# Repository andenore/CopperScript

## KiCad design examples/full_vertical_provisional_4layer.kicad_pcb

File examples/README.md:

# CopperScript examples

Each standalone example owns a directory so its source, local assets and
generated reference inputs stay together. The reusable component
packages under `packages/` are separate from these board and language examples.

| Example | Entry point |
| --- | --- |
| Antenna synthesis probe (first-order monopole template) | `antenna_synthesis/board.copper` |
| Coupling probe (antenna to a routed clock, `copper coupling`) | `coupling/board.copper` |
| Copper hard-macro definition | `macro_definition/board.copper` |
| Device model showcase | `device_model_showcase/board.copper` |
| Full vertical integration board | `full_vertical/board.copper` |
| FX10-like USB bridge, 121-ball 0.8 mm BGA (routing benchmark) | `fx10_bridge/board.copper` |
| Hierarchical board | `hierarchical_board/board.copper` |
| Invalid diagnostics fixture | `invalid_board/board.copper` |
| Mechanical anchors | `mechanical_anchors/board.copper` |
| Mechanical curves | `mechanical_curves/board.copper` |
| Mechanical editor demo | `mechanical_editor_demo/board.copper` |
| Mechanical outline | `mechanical_outline/board.copper` |
| Mechanical reference assets | `mechanical_reference/board.copper` |
| nRF52832 coin-cell board | `nrf52_coin_cell/board.copper` |
| nRF antenna hard-macro probe | `nrf_antenna_macro/board.copper` |
| TPS62130A regulator hard-macro probe | `tps62130a_macro/board.copper` |
| Resolved local footprint | `resolved_footprint_board/board.copper` |
| Valid compiler fixture | `valid_board/board.copper` |
| Analog front end (simulation removed) | [Source and recorded evidence](simulation/analog_frontend/README.md) |
| Soil impedance analyzer: battery board with the analog front end as a module, benches for the module | [Specification](simulation/impedance_analyzer/SPEC.md), [board, benches and results](simulation/impedance_analyzer/README.md) |
| Low-noise preamp: noise, Monte Carlo gain and worst-case offset benches | `simulation/preamp/board.copper` |
| Precision rectifier: a transient bench with a diode, op-amp clipping and slew, THD | `simulation/precision_rectifier/board.copper` |
| SPICE amplifier: an op-amp from a self-written SPICE model file (`sim spice`), op, AC, tran and noise benches | `simulation/spice_amplifier/board.copper` |
| Vendor models: TI's OPA810 PSpice model by URL and SHA-256 beside the built-in macro model (needs `copper models fetch`) | `simulation/vendor_models/board.copper` |

The CM4 carrier, managed-footprint, and simulation examples already use
multi-file directories and retain their existing folder names.

For a complete LED-ring board project, use
[CopperLedRing](https://github.com/andenore/CopperLedRing). It owns the current
board source, exact component selections, dependency pins and routing evidence.
Follow that project's build instructions and qualification status; its recorded
routing pass does not imply fabrication readiness.

Physical macro examples declare their bindings in `.copper` with ordinary asset
imports. Versions and hashes use the existing dependency workflow; the compiler
places and materializes those declarations without separately loading macro
scenes.

## Deprecated fixtures

`round_led_ring/board.copper` is deprecated in favor of CopperLedRing. It
remains for compiler regression tests and existing
commands, not as a second maintained LED-ring design or a routing benchmark.
See the [legacy fixture notes](../docs/round-led-ring.md).

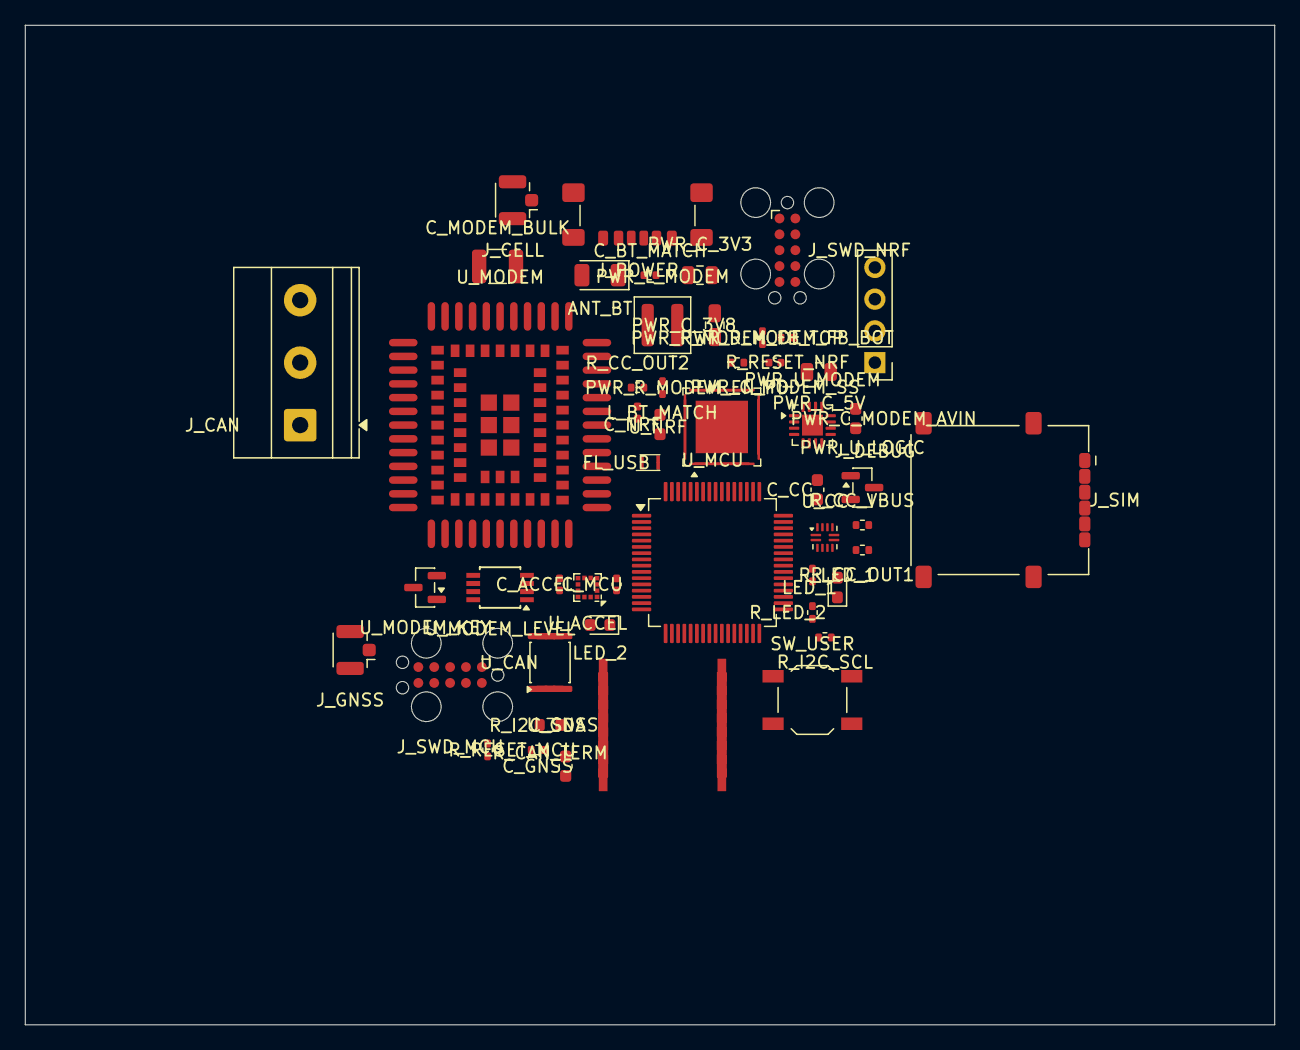
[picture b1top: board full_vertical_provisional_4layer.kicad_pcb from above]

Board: 4 copper layers, 100.0 x 80.0 mm, 51 parts (0 on the bottom side), 58 nets, no tracks yet.

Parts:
ANT_BT: RF_ANTENNA; Johanson_2450AT18x100
C_ACCEL: 1E+2 nF; C_0402_1005Metric
C_BT_MATCH: 0.8 pF; C_0402_1005Metric
C_CC: 1 uF; C_0603_1608Metric
C_GNSS: 1 uF; C_0603_1608Metric
C_MCU: 1E+2 nF; C_0402_1005Metric
C_MODEM_BULK: 1E+2 uF; C_1210_3225Metric
C_NRF: 4.7 uF; C_0603_1608Metric
FL_USB: COILCRAFT_0603USB_601MLC; L_CommonModeChoke_Coilcraft_0603USB
J_CAN: CAN_CONNECTOR; TerminalBlock_Phoenix_MKDS-1,5-3_1x03_P5.00mm_Horizontal
J_CELL: RF_CONNECTOR; U.FL_Hirose_U.FL-R-SMT-1_Vertical
J_DEBUG: DEBUG_UART_HEADER; PinHeader_1x04_P2.54mm_Vertical
J_GNSS: RF_CONNECTOR; U.FL_Hirose_U.FL-R-SMT-1_Vertical
J_POWER: GCT_USB4135_GF_A; USB_C_Receptacle_GCT_USB4135-GF-A_6P_TopMnt_Horizontal
J_SIM: SIM8060_6_0_14_00_A; nanoSIM_GCT_SIM8060-6-0-14-00
J_SWD_MCU: SWD_HEADER; Tag-Connect_TC2050-IDC-FP_2x05_P1.27mm_Vertical
J_SWD_NRF: SWD_HEADER; Tag-Connect_TC2050-IDC-FP_2x05_P1.27mm_Vertical
LED_1, LED_2: LED; LED_0603_1608Metric
L_BT_MATCH: 3.9 nH; L_0402_1005Metric
PWR_C_3V3, PWR_C_3V8: 22 uF; C_0805_2012Metric
PWR_C_5V: 1E+1 uF; C_0805_2012Metric
PWR_C_MODEM_AVIN: 1E+2 nF; C_0603_1608Metric
PWR_C_MODEM_SS: 3.3 nF; C_0402_1005Metric
PWR_L_MODEM: XAL4020_222MEC; L_Coilcraft_XAL4020-XXX
PWR_R_MODEM_EN_PD: 1E+2 kohm; R_0402_1005Metric
PWR_R_MODEM_FB_BOT: 2E+2 kohm; R_0402_1005Metric
PWR_R_MODEM_FB_TOP: 7.5E+2 kohm; R_0402_1005Metric
PWR_U_LOGIC: REGULATOR_3V3; SOT-23
PWR_U_MODEM: TPS62130ARGTR; VQFN-16-1EP_3x3mm_P0.5mm_EP1.68x1.68mm
R_CAN_TERM: 1.2E+2 ohm; R_0603_1608Metric
R_CC_OUT1, R_CC_OUT2: 1E+1 kohm; R_0402_1005Metric
R_CC_VBUS: 9E+2 kohm; R_0402_1005Metric
R_I2C_SCL, R_I2C_SDA: 4.7 kohm; R_0402_1005Metric
R_LED_1, R_LED_2: 1 kohm; R_0402_1005Metric
R_RESET_MCU: 1E+1 kohm; R_0402_1005Metric
R_RESET_NRF: 1E+1 kohm; R_0402_1005Metric
SW_USER: BUTTON; SW_SPST_TL3342
U_ACCEL: LIS2DW12; LGA-12_2x2mm_P0.5mm
U_CAN: TCAN334G; VSSOP-8_3x3mm_P0.65mm
U_CC: TUSB320LAI; Texas_X2QFN-12_1.6x1.6mm_P0.4mm
U_GNSS: MAX_M10S_00B; u-blox_MAX-M10S
U_MCU: STM32G0C1RET6; LQFP-64_10x10mm_P0.5mm
U_MODEM: EG800G_EU; Quectel_EG800G
U_MODEM_KEY: OPEN_DRAIN_DRIVER; SOT-23
U_MODEM_LEVEL: DUAL_UART_LEVEL_SHIFTER; TSSOP-8_3x3mm_P0.65mm
U_NRF: NRF52832_QFAA; QFN-48-1EP_6x6mm_P0.4mm_EP4.2x4.2mm

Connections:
ACCEL_INT: U_ACCEL.12, U_MCU.15
CAN_H: J_CAN.1, R_CAN_TERM.1, U_CAN.7
CAN_L: J_CAN.2, R_CAN_TERM.2, U_CAN.6
CAN_RX: U_CAN.4, U_MCU.25
CAN_TX: U_CAN.1, U_MCU.26
CELL_RF: J_CELL.1, U_MODEM.35
DEBUG_RX: J_DEBUG.3, U_MCU.22
DEBUG_TX: J_DEBUG.2, U_MCU.21
GND: ANT_BT.2, C_ACCEL.2, C_BT_MATCH.2, C_CC.2, C_GNSS.2, C_MCU.2, C_MODEM_BULK.2, C_NRF.2, J_CAN.3, J_CELL.2, J_DEBUG.4, J_GNSS.2, J_POWER.A12, J_POWER.B12, J_POWER.SH, J_SIM.5, J_SIM.SH, J_SWD_MCU.3, J_SWD_MCU.5, J_SWD_NRF.3, J_SWD_NRF.5, LED_1.2, LED_2.2, PWR_C_3V3.2, PWR_C_3V8.2, PWR_C_5V.2, PWR_C_MODEM_AVIN.2, PWR_C_MODEM_SS.2, PWR_R_MODEM_EN_PD.2, PWR_R_MODEM_FB_BOT.2, PWR_U_LOGIC.2, PWR_U_MODEM.6, PWR_U_MODEM.7, PWR_U_MODEM.8, PWR_U_MODEM.15, PWR_U_MODEM.16, PWR_U_MODEM.17, SW_USER.2, U_ACCEL.3, U_ACCEL.6, U_ACCEL.7, U_ACCEL.8, U_CAN.2, U_CAN.5, U_CAN.8, U_CC.3, U_CC.10, U_CC.11, U_GNSS.1, U_GNSS.10, U_GNSS.12, U_MCU.9, U_MODEM.1, U_MODEM.10, U_MODEM.27, U_MODEM.34, U_MODEM.36, U_MODEM.37, U_MODEM.40, U_MODEM.41, U_MODEM.45, U_MODEM.46, U_MODEM.47, U_MODEM.48, U_MODEM.70, U_MODEM.71, U_MODEM.72, U_MODEM.73, U_MODEM.88, U_MODEM.89, U_MODEM.90, U_MODEM.91, U_MODEM.92, U_MODEM.93, U_MODEM.94, U_MODEM.95, U_MODEM_KEY.2, U_MODEM_LEVEL.4, U_NRF.31, U_NRF.45, U_NRF.49
GNSS_RF: J_GNSS.1, U_GNSS.11
GNSS_RX: U_GNSS.3, U_MCU.19
GNSS_TIMEPULSE: U_GNSS.4, U_MCU.16
GNSS_TX: U_GNSS.2, U_MCU.20
I2C_SCL: R_I2C_SCL.2, U_ACCEL.1, U_MCU.24
I2C_SDA: R_I2C_SDA.2, U_ACCEL.4, U_MCU.23
MCU_MODEM_RX: U_MCU.61, U_MODEM_LEVEL.3
MCU_MODEM_TX: U_MCU.60, U_MODEM_LEVEL.2
MCU_NRF_RX: U_MCU.63, U_NRF.8
MCU_NRF_TX: U_MCU.62, U_NRF.10
MCU_RESET: J_SWD_MCU.10, R_RESET_MCU.2, U_MCU.12
MCU_SWDCLK: J_SWD_MCU.4, U_MCU.46
MCU_SWDIO: J_SWD_MCU.2, U_MCU.45
MODEM_EN: PWR_R_MODEM_EN_PD.1, PWR_U_MODEM.13, U_MCU.64
MODEM_PWRKEY: U_MODEM.7, U_MODEM_KEY.3
MODEM_PWRKEY_CTL: U_MCU.13, U_MODEM_KEY.1
MODEM_STATUS: U_MCU.14, U_MODEM.25
MODEM_UART_RX: U_MODEM.17, U_MODEM_LEVEL.5
MODEM_UART_TX: U_MODEM.18, U_MODEM_LEVEL.6
NRF_RESET: J_SWD_NRF.10, R_RESET_NRF.2, U_NRF.24
NRF_RF_ANT: ANT_BT.1, C_BT_MATCH.1, L_BT_MATCH.2
NRF_RF_RAW: L_BT_MATCH.1, U_NRF.30
NRF_SWDCLK: J_SWD_NRF.4, U_NRF.25
NRF_SWDIO: J_SWD_NRF.2, U_NRF.26
PWR/MODEM_FB: PWR_R_MODEM_FB_BOT.1, PWR_R_MODEM_FB_TOP.2, PWR_U_MODEM.5
PWR/MODEM_SS: PWR_C_MODEM_SS.1, PWR_U_MODEM.9
PWR/MODEM_SW: PWR_L_MODEM.1, PWR_U_MODEM.1, PWR_U_MODEM.2, PWR_U_MODEM.3
SIM_CLK: J_SIM.3, U_MODEM.13
SIM_IO: J_SIM.7, U_MODEM.11
SIM_RST: J_SIM.2, U_MODEM.12
SIM_VCC: J_SIM.1, U_MODEM.14
USB_C_CC1: J_POWER.A5, U_CC.1
USB_C_CC2: J_POWER.B5, U_CC.2
USB_C_CURRENT_1: R_CC_OUT1.2, U_CC.7, U_MCU.48
USB_C_CURRENT_2: R_CC_OUT2.2, U_CC.8, U_MCU.49
USB_C_VBUS_DET: R_CC_VBUS.2, U_CC.4
USB_DM_MCU: FL_USB.2, U_MCU.43
USB_DM_MODEM: FL_USB.3, U_MODEM.60
USB_DP_MCU: FL_USB.1, U_MCU.44
USB_DP_MODEM: FL_USB.4, U_MODEM.59
USER_BUTTON: SW_USER.1, U_MCU.3
USER_LED_1: R_LED_1.1, U_MCU.38
USER_LED_1_A: LED_1.1, R_LED_1.2
USER_LED_2: R_LED_2.1, U_MCU.39
USER_LED_2_A: LED_2.1, R_LED_2.2
V1V8_MODEM: U_MODEM.24, U_MODEM_LEVEL.8
V3V3: C_ACCEL.1, C_CC.1, C_GNSS.1, C_MCU.1, C_NRF.1, J_DEBUG.1, J_SWD_MCU.1, J_SWD_NRF.1, PWR_C_3V3.1, PWR_U_LOGIC.3, R_CC_OUT1.1, R_CC_OUT2.1, R_I2C_SCL.1, R_I2C_SDA.1, R_RESET_MCU.1, R_RESET_NRF.1, U_ACCEL.2, U_ACCEL.9, U_ACCEL.10, U_CAN.3, U_CC.12, U_GNSS.6, U_GNSS.7, U_GNSS.8, U_MCU.6, U_MCU.7, U_MCU.8, U_MODEM_LEVEL.1, U_MODEM_LEVEL.7, U_NRF.13, U_NRF.36, U_NRF.48
V3V8: C_MODEM_BULK.1, PWR_C_3V8.1, PWR_L_MODEM.2, PWR_R_MODEM_FB_TOP.1, PWR_U_MODEM.14, U_MODEM.42, U_MODEM.43
V5: J_POWER.A9, J_POWER.B9, PWR_C_5V.1, PWR_C_MODEM_AVIN.1, PWR_U_LOGIC.1, PWR_U_MODEM.10, PWR_U_MODEM.11, PWR_U_MODEM.12, R_CC_VBUS.1, U_MODEM.61

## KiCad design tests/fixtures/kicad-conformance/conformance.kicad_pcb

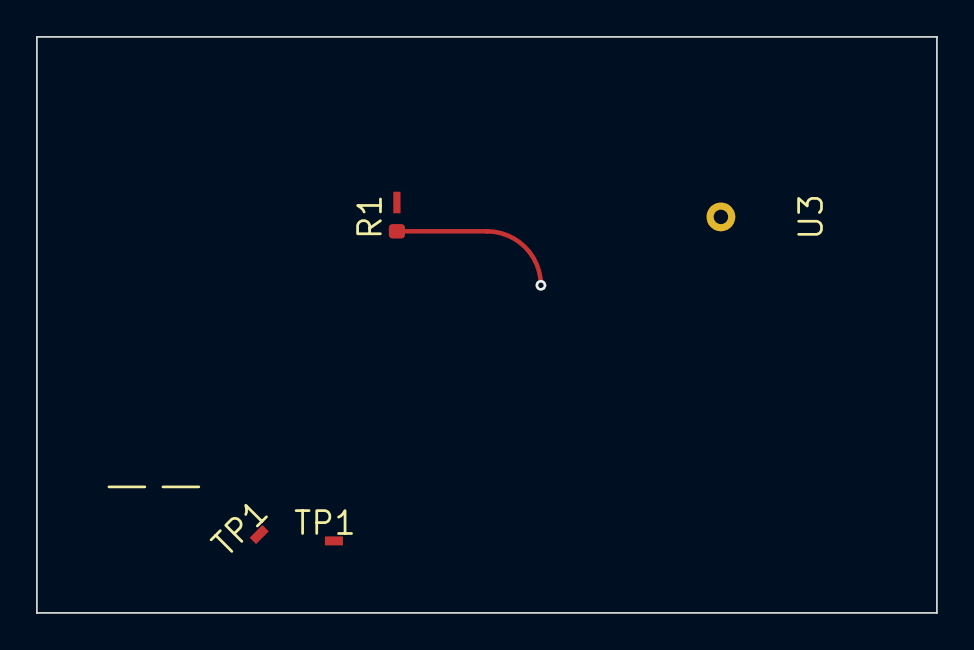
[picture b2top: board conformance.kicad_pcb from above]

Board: 2 copper layers, 50.0 x 32.0 mm, 5 parts (1 on the bottom side), 2 nets.

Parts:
R1: 10k; R_0603
TP1, TP1#2: TestPoint
U2: SOT23_Back
U3: Module_Keepout

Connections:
GND: R1.1, U2.3, U3.1
SIG: R1.2, TP1.1, TP1#2.1, U2.1

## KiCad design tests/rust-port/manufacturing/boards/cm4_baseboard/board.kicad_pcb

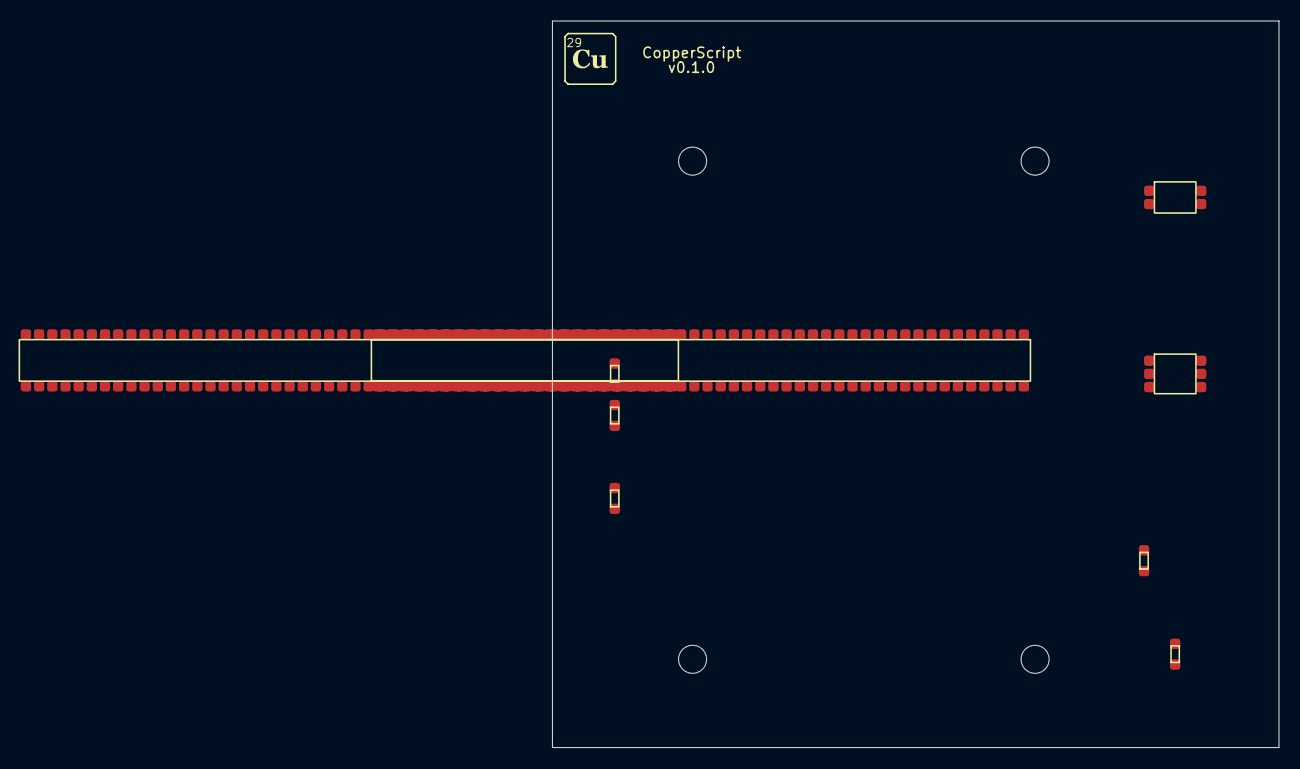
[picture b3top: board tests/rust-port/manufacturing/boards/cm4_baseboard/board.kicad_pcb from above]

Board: 4 copper layers, 70.0 x 70.0 mm, 13 parts (0 on the bottom side), 12 nets, no tracks yet.

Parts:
CS_MH_4e76aa086c1c0c76, CS_MH_46dff4b017b65127, CS_MH_57f5d33d8441581a: mechanical_hole_2700000__704487c97c5e890e1efa
CS_MH_a25b90a7272961f0: mechanical_hole_2700000__704487c97c5e890e1efa
C_VREF: 100 nF; Capacitor_SMD_C_0402_1005Metric_3bdc543a41__36df095855c7baa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
D1: KENTO_KT0603R; KENTO_KENTO_KT0603R_c41109b3dd__5e56d2dd6d7a4f36240d
J_CM4_GPIO, J_CM4_HS: DF40C-100DS-0.4V(51); github_com_andenore_CopperLib_packages_profiles_raspberry_p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
J_ENABLE: GLOBAL_EN / GND: short to power off; Connector_PinHeader_2_54mm_PinHeader_1x02_P2_54mm_Vertical_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
J_GPIO: 3V3 / GPIO2 / GPIO3 / GPIO17 / GPIO27 / GND; Connector_PinHeader_2_54mm_PinHeader_1x06_P2_54mm_Vertical_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
J_POWER: 5V IN / GND; Connector_PinHeader_2_54mm_PinHeader_1x02_P2_54mm_Vertical_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
J_UART: 3V3 sense / TX / RX / GND; Connector_PinHeader_2_54mm_PinHeader_1x04_P2_54mm_Vertical_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
R_LED: 10 kohm; Resistor_SMD_R_0603_1608Metric_4cb9c1d429__23516488a272ae66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

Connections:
ACT_LED_A: D1.1, R_LED.2
ACT_LED_K: D1.2, J_CM4_GPIO.21
CM4_RX: J_CM4_GPIO.51, J_UART.3
CM4_TX: J_CM4_GPIO.55, J_UART.2
GLOBAL_EN: J_CM4_GPIO.99, J_ENABLE.1
GND: C_VREF.2, J_CM4_GPIO.1, J_CM4_GPIO.2, J_CM4_GPIO.7, J_CM4_GPIO.8, J_CM4_GPIO.13, J_CM4_GPIO.14, J_CM4_GPIO.22, J_CM4_GPIO.23, J_CM4_GPIO.32, J_CM4_GPIO.33, J_CM4_GPIO.42, J_CM4_GPIO.43, J_CM4_GPIO.52, J_CM4_GPIO.53, J_CM4_GPIO.59, J_CM4_GPIO.60, J_CM4_GPIO.65, J_CM4_GPIO.66, J_CM4_GPIO.71, J_CM4_GPIO.74, J_CM4_GPIO.98, J_CM4_HS.7, J_CM4_HS.8, J_CM4_HS.13, J_CM4_HS.14, J_CM4_HS.19, J_CM4_HS.20, J_CM4_HS.25, J_CM4_HS.26, J_CM4_HS.31, J_CM4_HS.32, J_CM4_HS.37, J_CM4_HS.38, J_CM4_HS.44, J_CM4_HS.50, J_CM4_HS.55, J_CM4_HS.56, J_CM4_HS.61, J_CM4_HS.62, J_CM4_HS.67, J_CM4_HS.68, J_CM4_HS.73, J_CM4_HS.74, J_CM4_HS.79, J_CM4_HS.80, J_CM4_HS.85, J_CM4_HS.86, J_CM4_HS.91, J_CM4_HS.92, J_CM4_HS.97, J_CM4_HS.98, J_ENABLE.2, J_GPIO.6, J_POWER.2, J_UART.4
GPIO2: J_CM4_GPIO.58, J_GPIO.2
GPIO3: J_CM4_GPIO.56, J_GPIO.3
GPIO17: J_CM4_GPIO.50, J_GPIO.4
GPIO27: J_CM4_GPIO.48, J_GPIO.5
V3V3: C_VREF.1, J_CM4_GPIO.78, J_CM4_GPIO.84, J_CM4_GPIO.86, J_GPIO.1, J_UART.1, R_LED.1
V5: J_CM4_GPIO.77, J_CM4_GPIO.79, J_CM4_GPIO.81, J_CM4_GPIO.83, J_CM4_GPIO.85, J_CM4_GPIO.87, J_POWER.1

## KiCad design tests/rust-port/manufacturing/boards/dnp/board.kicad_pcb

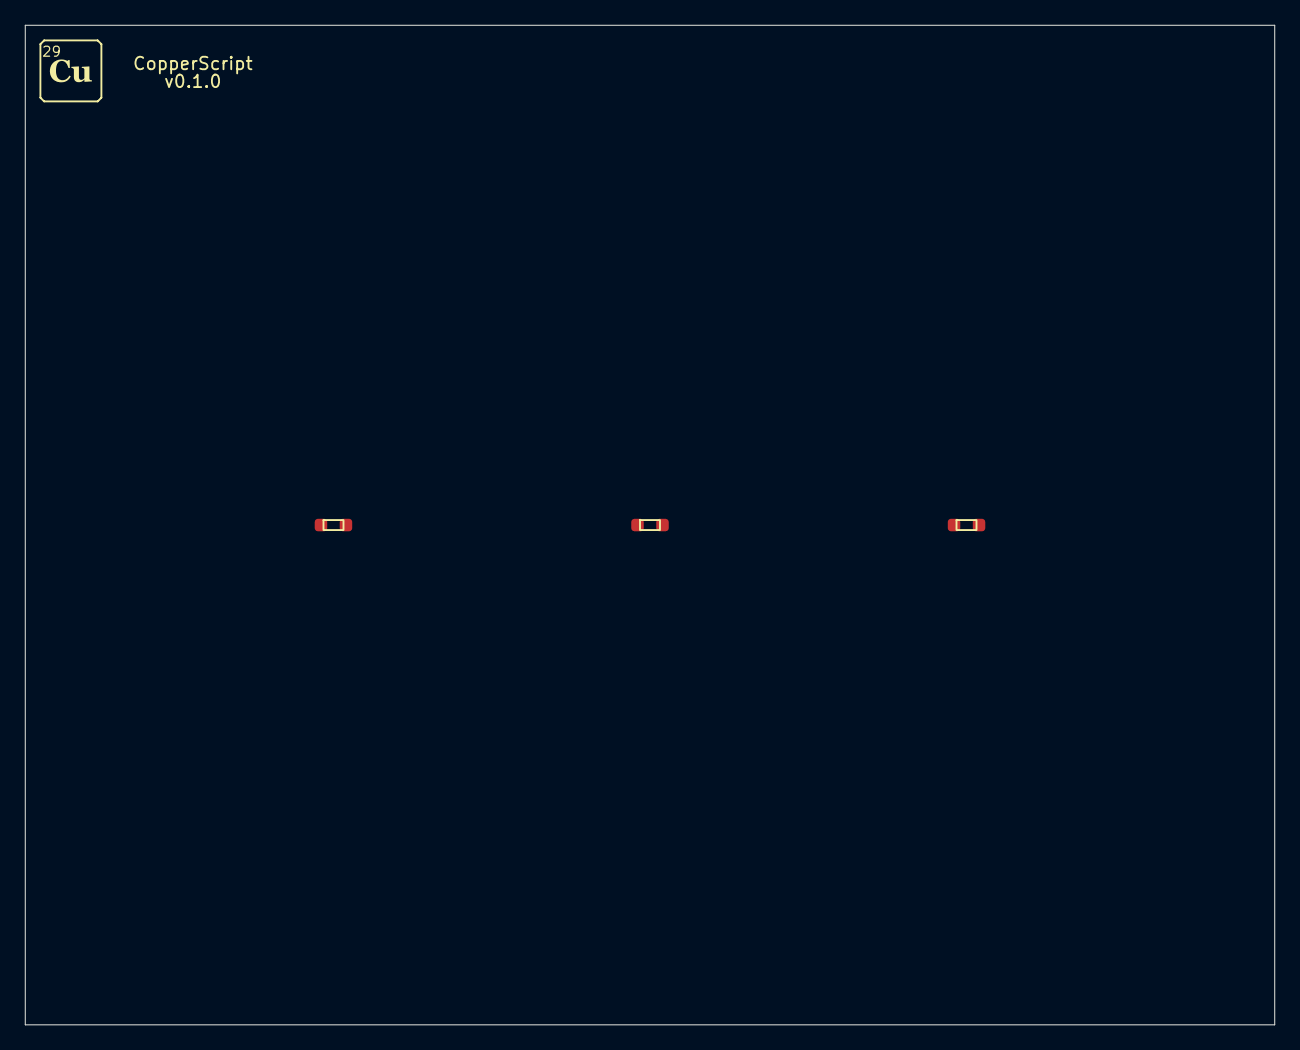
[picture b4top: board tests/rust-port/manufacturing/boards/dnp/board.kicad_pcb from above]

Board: 2 copper layers, 100.0 x 80.0 mm, 3 parts (0 on the bottom side), 2 nets, no tracks yet.

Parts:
C_DNP: DNP; Resistor_SMD_R_0402_1005Metric_fdb7f701ac__unassembled__f69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
R1, R2: Fitted; Resistor_SMD_R_0402_1005Metric_ea21fd0be2__078150e45b6b77ac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

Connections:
GND: C_DNP.2, R1.2, R2.2
SIGNAL: C_DNP.1, R1.1, R2.1

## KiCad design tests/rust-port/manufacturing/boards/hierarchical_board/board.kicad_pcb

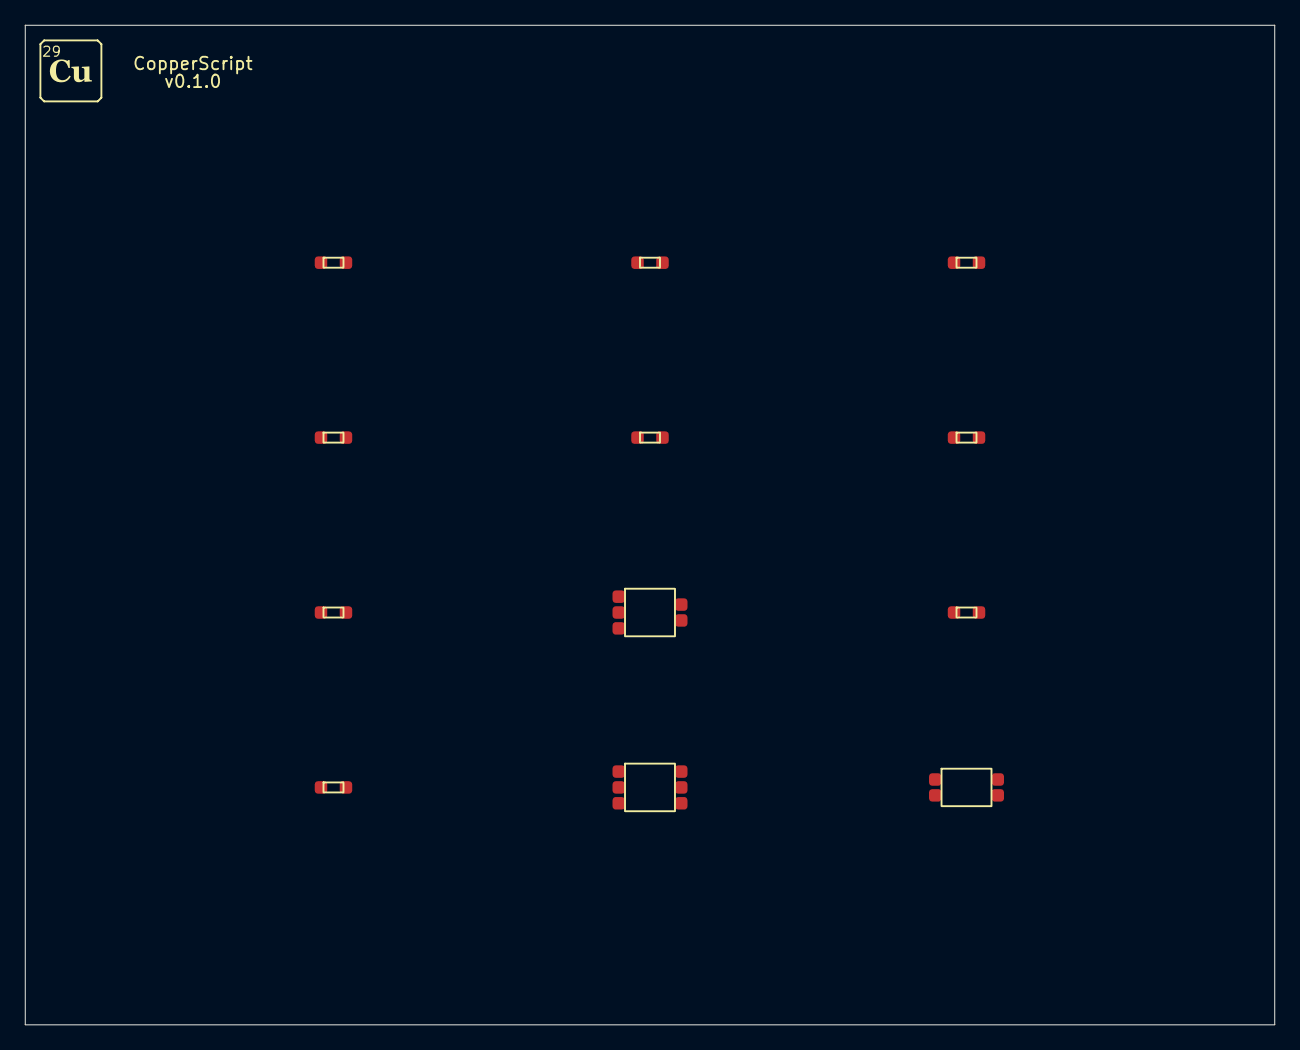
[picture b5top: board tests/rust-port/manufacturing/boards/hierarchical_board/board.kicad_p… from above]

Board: 2 copper layers, 100.0 x 80.0 mm, 12 parts (0 on the bottom side), 7 nets, no tracks yet.

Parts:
C1: 100 nF; 0402_9c2134b530__0fb0bb9a2e0077d858db
PWR_C_IN: 10 uF; 0603_81c387e6e1__c7736b0d8ecf520b0523
PWR_C_OUT: 22 uF; 0603_81c387e6e1__c7736b0d8ecf520b0523
PWR_D1: 40 V Schottky; SOD_123_efa837de2e__cfb0d4e968d0b264e214
PWR_L1: 10 uH; L_4x4mm_7af7df88b8__6a048950ee45cd71650c
PWR_R_BOTTOM: 31.6 kohm; 0402_b4527f9b21__9b192bf2ecd33fdeea18
PWR_R_TOP: 100 kohm; 0402_b4527f9b21__9b192bf2ecd33fdeea18
PWR_U1: 5 V to 3.3 V buck; SOT_23_5_1a109a2ec2__6e889cd8a0e923c7e456
R1, R2: 4.7 kohm; 0402_b4527f9b21__9b192bf2ecd33fdeea18
U1: STM32G0B1CBT6; LQFP_48_f42af30189__71b94d8e6008976dbf1f
U2: BME280; LGA_8_40352dfb0d__fcaac17623b50b27bffa

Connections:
GND: C1.2, PWR_C_IN.2, PWR_C_OUT.2, PWR_D1.1, PWR_R_BOTTOM.2, PWR_U1.2, U1.23, U2.2
I2C_SCL: R2.2, U1.45, U2.3
I2C_SDA: R1.2, U1.46, U2.4
PWR/FEEDBACK: PWR_R_BOTTOM.1, PWR_R_TOP.2, PWR_U1.4
PWR/SWITCH: PWR_D1.2, PWR_L1.1, PWR_U1.3
V3V3: C1.1, PWR_C_OUT.1, PWR_L1.2, PWR_R_TOP.1, R1.1, R2.1, U1.24, U2.1
VBUS: PWR_C_IN.1, PWR_U1.1, PWR_U1.5

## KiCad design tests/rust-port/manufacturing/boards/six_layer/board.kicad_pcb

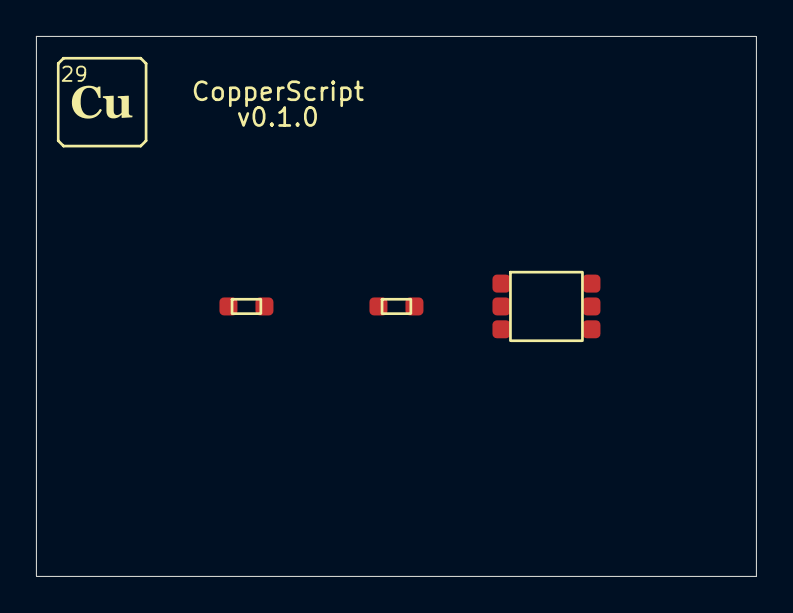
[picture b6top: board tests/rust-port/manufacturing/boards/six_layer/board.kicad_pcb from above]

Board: 6 copper layers, 40.0 x 30.0 mm, 3 parts (0 on the bottom side), 2 nets, no tracks yet.

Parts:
C1: 100 nF; 0402_9c2134b530__0fb0bb9a2e0077d858db
PS1: VOLTAGE_SOURCE; SOT_23_b818d02061__00451b3eeeeeadf5b295
U1: STM32_LIKE; LQFP_48_1857f4a7dd__18a179d3975fdd3a79ec

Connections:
GND: C1.2, PS1.2, U1.2
V3V3: C1.1, PS1.1, U1.1

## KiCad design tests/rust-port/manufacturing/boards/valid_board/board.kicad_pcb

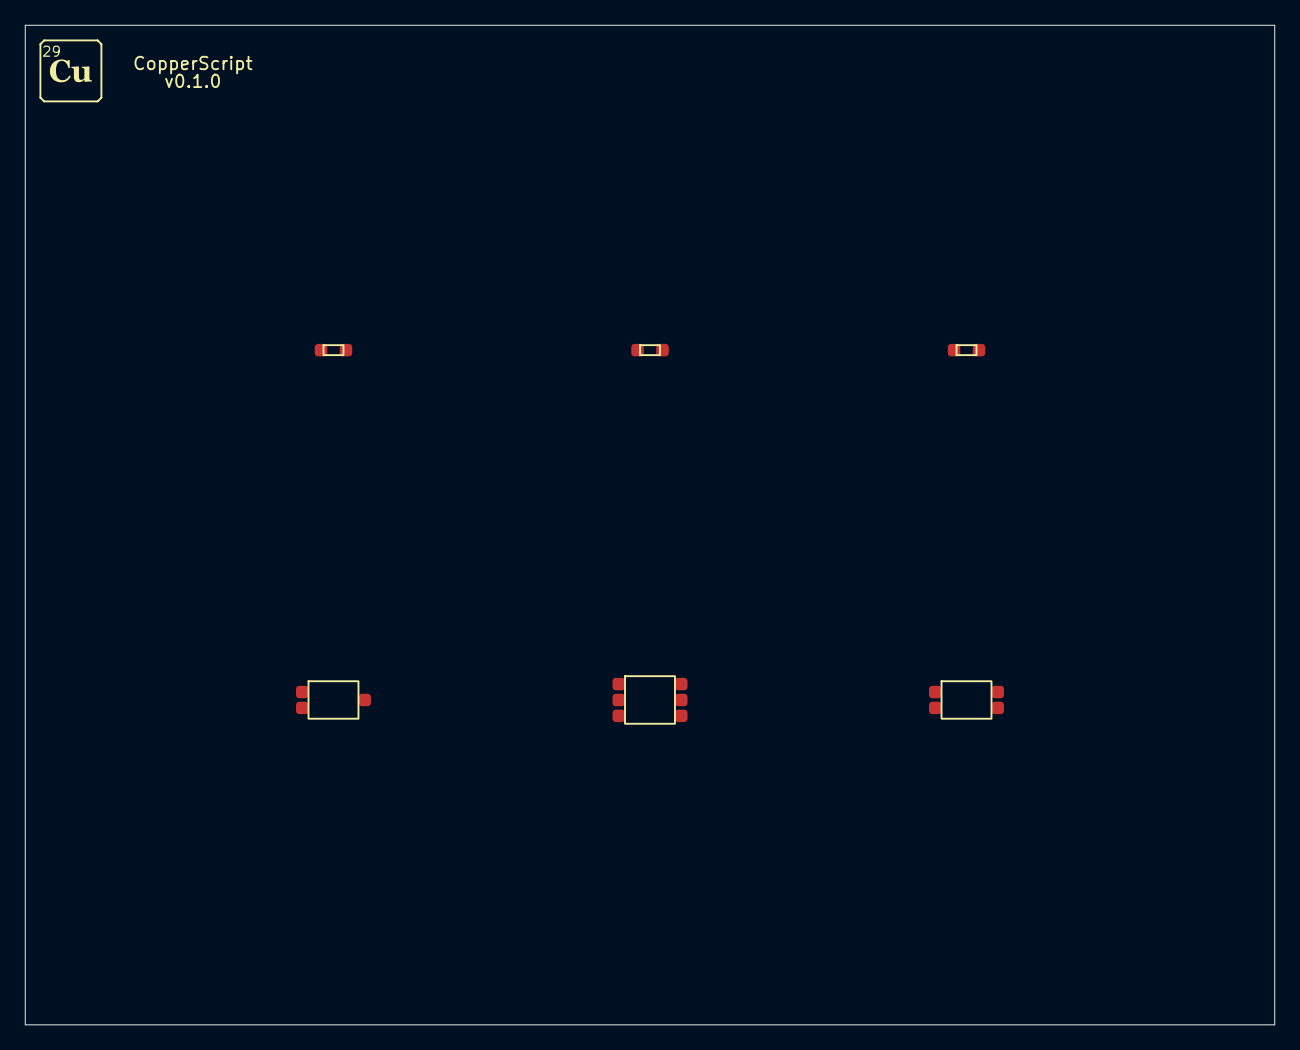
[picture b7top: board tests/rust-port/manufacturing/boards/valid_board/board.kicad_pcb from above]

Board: 2 copper layers, 100.0 x 80.0 mm, 6 parts (0 on the bottom side), 4 nets, no tracks yet.

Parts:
C1: 100 nF; 0402_9c2134b530__0fb0bb9a2e0077d858db
R1, R2: 4.7 kohm; 0402_b4527f9b21__9b192bf2ecd33fdeea18
U1: REGULATOR_3V3; SOT_23_3_d497cde594__216aa7294530fdcf69b5
U2: STM32G0B1CBT6; LQFP_48_f42af30189__71b94d8e6008976dbf1f
U3: BME280; LGA_8_40352dfb0d__fcaac17623b50b27bffa

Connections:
GND: C1.2, U1.2, U2.23, U3.2
I2C_SCL: R2.2, U2.45, U3.3
I2C_SDA: R1.2, U2.46, U3.4
V3V3: C1.1, R1.1, R2.1, U1.3, U2.24, U3.1
